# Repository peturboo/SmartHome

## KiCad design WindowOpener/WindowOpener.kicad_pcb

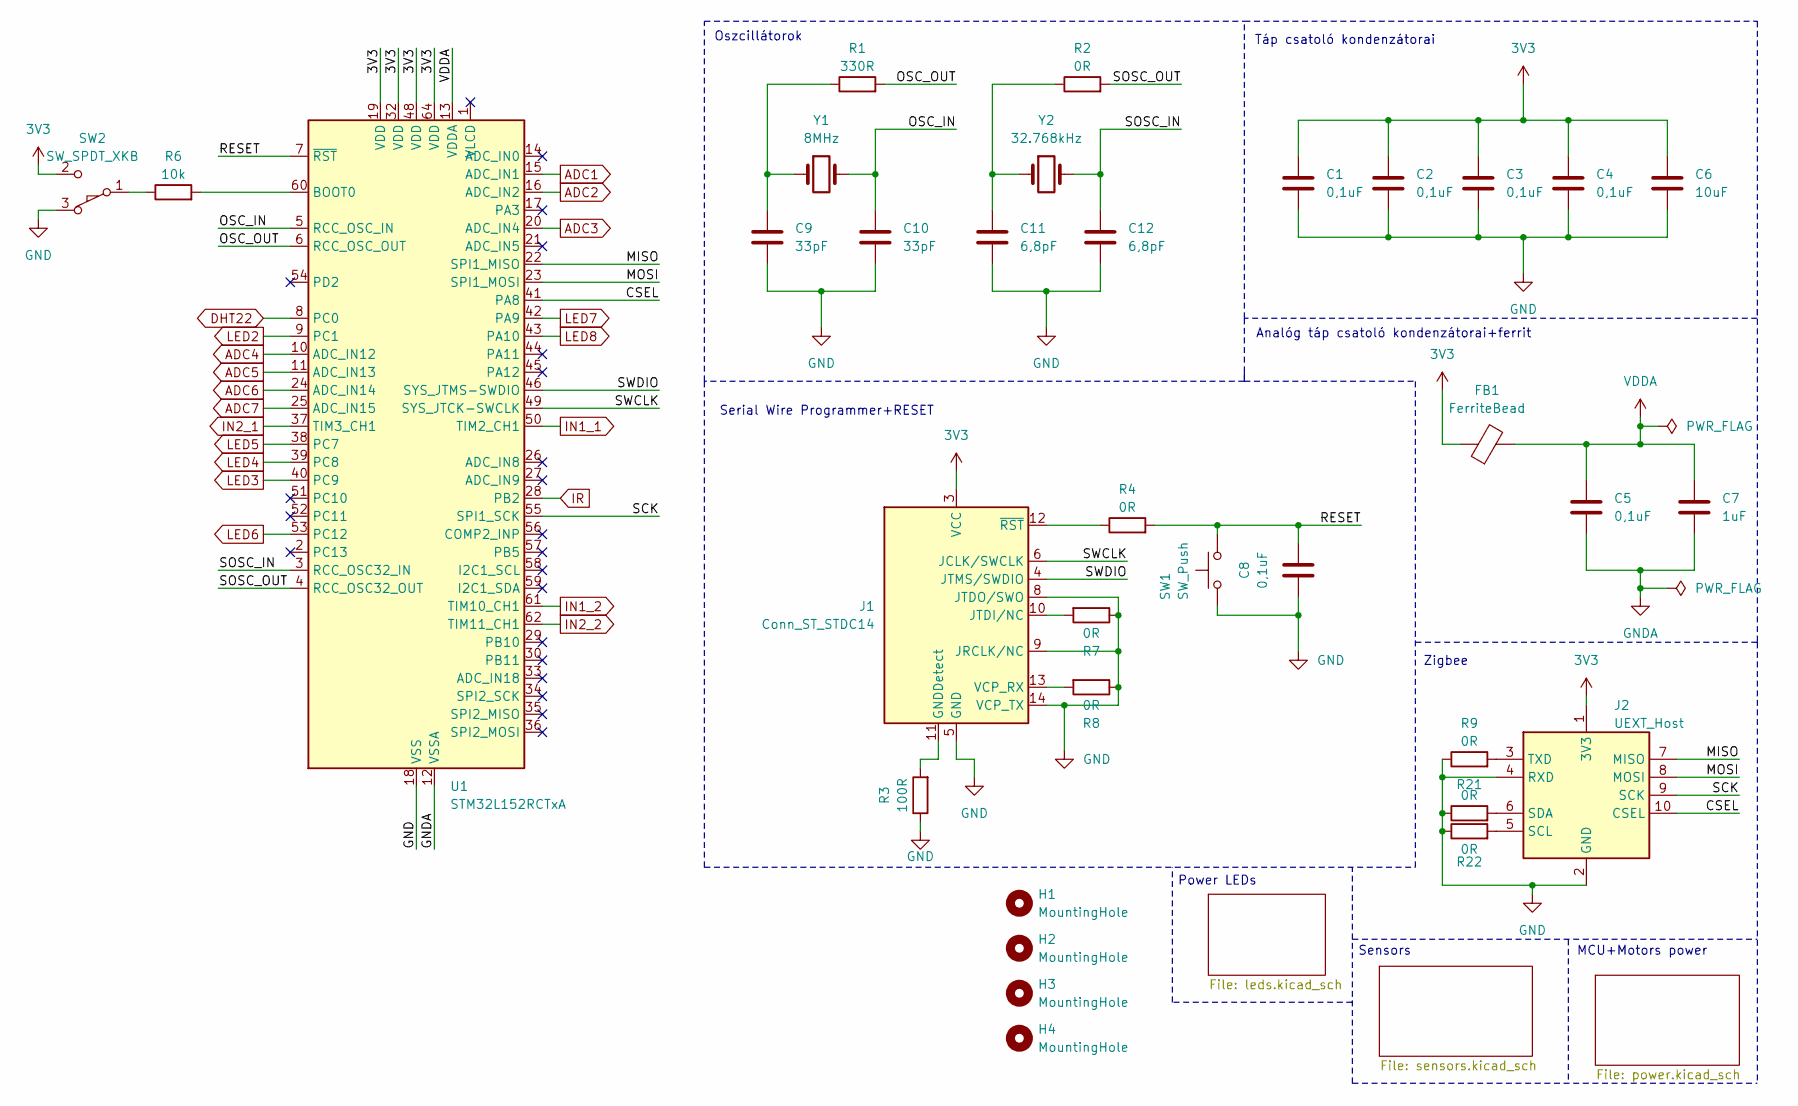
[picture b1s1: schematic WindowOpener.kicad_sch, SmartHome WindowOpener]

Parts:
C1, C2, C3, C4, C5, C8: 0,1uF; C_1206_3216Metric_Pad1.33x1.80mm_HandSolder
C6: 10uF; C_1206_3216Metric_Pad1.33x1.80mm_HandSolder
C7: 1uF; C_2220_5750Metric_Pad1.97x5.40mm_HandSolder
C9, C10: 33pF; C_1206_3216Metric_Pad1.33x1.80mm_HandSolder
C11, C12: 6,8pF; C_1206_3216Metric_Pad1.33x1.80mm_HandSolder
FB1: FerriteBead; L_Axial_L9.5mm_D4.0mm_P12.70mm_Horizontal_Fastron_SMCC
H1, H2, H3, H4: MountingHole; MountingHole_5.3mm_M5
J1: Conn_ST_STDC14; PinHeader_2x07_P1.27mm_Vertical
J2: UEXT_Host; PinHeader_2x05_P2.54mm_Vertical
R1: 330R; R_2010_5025Metric_Pad1.40x2.65mm_HandSolder
R2, R4, R7, R8, R9, R21, R22: 0R; R_2010_5025Metric_Pad1.40x2.65mm_HandSolder
R3: 100R; R_2010_5025Metric_Pad1.40x2.65mm_HandSolder
R6: 10k; R_2010_5025Metric_Pad1.40x2.65mm_HandSolder
SW1: SW_Push; SW_Push_1P1T_NO_CK_KMR2
SW2: SW_SPDT_XKB; SW_XKB_DM1-16UP-1
U1: STM32L152RCTxA; LQFP-64_10x10mm_P0.5mm
Y1: 8MHz; Crystal_HC49-U_Vertical
Y2: 32.768kHz; Crystal_C26-LF_D2.1mm_L6.5mm_Vertical

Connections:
3V3: C1.1, C2.1, C3.1, C4.1, C6.1, FB1.1, J1.3 (VCC), J2.1 (3V3), SW2.2 (B), U1.19 (VDD), U1.32 (VDD), U1.48 (VDD), U1.64 (VDD); also elsewhere on the board
/CSEL: J2.10 (CSEL), U1.41 (PA8)
/MISO: J2.7 (MISO), U1.22 (SPI1_MISO)
/MOSI: J2.8 (MOSI), U1.23 (SPI1_MOSI)
/OSC_IN: C10.1, U1.5 (RCC_OSC_IN), Y1.2
/OSC_OUT: R1.2, U1.6 (RCC_OSC_OUT)
/RESET: C8.2, R4.2, SW1.2, U1.7 (~RST)
/SCK: J2.9 (SCK), U1.55 (SPI1_SCK)
/SOSC_IN: C12.1, U1.3 (RCC_OSC32_IN), Y2.2
/SOSC_OUT: R2.2, U1.4 (RCC_OSC32_OUT)
/SWCLK: J1.6 (JCLK/SWCLK), U1.49 (SYS_JTCK-SWCLK)
/SWDIO: J1.4 (JTMS/SWDIO), U1.46 (SYS_JTMS-SWDIO)
ADC1: U1.15 (ADC_IN1); also elsewhere on the board
ADC2: U1.16 (ADC_IN2); also elsewhere on the board
ADC3: U1.20 (ADC_IN4); also elsewhere on the board
ADC4: U1.10 (ADC_IN12); also elsewhere on the board
ADC5: U1.11 (ADC_IN13); also elsewhere on the board
ADC6: U1.24 (ADC_IN14); also elsewhere on the board
ADC7: U1.25 (ADC_IN15); also elsewhere on the board
DHT22: U1.8 (PC0); also elsewhere on the board
GND: C1.2, C2.2, C3.2, C4.2, C6.2, C8.1, C9.2, C10.2, C11.2, C12.2, J1.5 (GND), J1.7 (GND), J1.8 (JTDO/SWO), J1.9 (JRCLK/NC), J1.14 (VCP_TX), J2.2 (GND), J2.4 (RXD), R3.1, R7.1, R8.1, R9.1, R21.1, R22.1, SW1.1, SW2.3 (C), U1.18 (VSS), U1.31 (VSS), U1.47 (VSS), U1.63 (VSS); also elsewhere on the board
GNDA: C5.2, C7.2, U1.12 (VSSA)
IN1_1: U1.50 (TIM2_CH1); also elsewhere on the board
IN1_2: U1.61 (TIM10_CH1); also elsewhere on the board
IN2_1: U1.37 (TIM3_CH1); also elsewhere on the board
IN2_2: U1.62 (TIM11_CH1); also elsewhere on the board
IR: U1.28 (PB2); also elsewhere on the board
LED2: U1.9 (PC1); also elsewhere on the board
LED3: U1.40 (PC9); also elsewhere on the board
LED4: U1.39 (PC8); also elsewhere on the board
LED5: U1.38 (PC7); also elsewhere on the board
LED6: U1.53 (PC12); also elsewhere on the board
LED7: U1.42 (PA9); also elsewhere on the board
LED8: U1.43 (PA10); also elsewhere on the board
unnamed: C9.1, R1.1, Y1.1
unnamed: C11.1, R2.1, Y2.1
unnamed: J1.11 (GNDDetect), R3.2
unnamed: J1.10 (JTDI/NC), R7.2
unnamed: J1.13 (VCP_RX), R8.2
unnamed: J1.12 (~RST), R4.1
unnamed: J2.5 (SCL), R22.2
unnamed: J2.6 (SDA), R21.2
unnamed: J2.3 (TXD), R9.2
unnamed: R6.1, SW2.1 (A)
unnamed: R6.2, U1.60 (BOOT0)
VDDA: C5.1, C7.1, FB1.2, U1.13 (VDDA)

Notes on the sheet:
Sensors
Zigbee
Serial Wire Programmer+RESET
Analóg táp csatoló kondenzátorai+ferrit
Oszcillátorok
MCU+Motors power
Táp csatoló kondenzátorai
Power LEDs

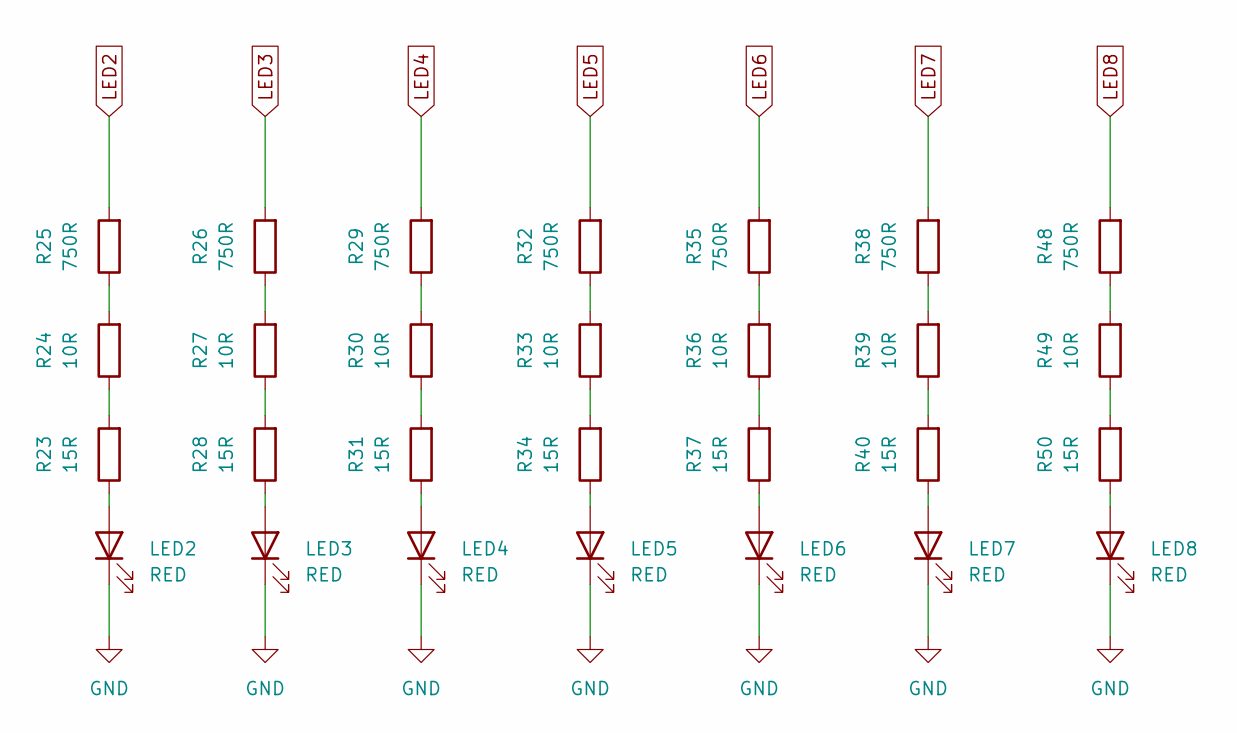
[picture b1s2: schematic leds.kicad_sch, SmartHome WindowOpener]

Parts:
LED2, LED3, LED4, LED5, LED6, LED7, LED8: RED; LED_1206_3216Metric_Pad1.42x1.75mm_HandSolder
R23, R28, R31, R34, R37, R40, R50: 15R; R_1210_3225Metric_Pad1.30x2.65mm_HandSolder
R24, R27, R30, R33, R36, R39, R49: 10R; R_1206_3216Metric_Pad1.30x1.75mm_HandSolder
R25, R26, R29, R32, R35, R38, R48: 750R; R_1206_3216Metric_Pad1.30x1.75mm_HandSolder

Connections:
GND: LED2.1 (K), LED3.1 (K), LED4.1 (K), LED5.1 (K), LED6.1 (K), LED7.1 (K), LED8.1 (K); also elsewhere on the board
LED2: R25.2; also elsewhere on the board
LED3: R26.2; also elsewhere on the board
LED4: R29.2; also elsewhere on the board
LED5: R32.2; also elsewhere on the board
LED6: R35.2; also elsewhere on the board
LED7: R38.2; also elsewhere on the board
LED8: R48.2; also elsewhere on the board
unnamed: LED2.2 (A), R23.1
unnamed: LED3.2 (A), R28.1
unnamed: LED4.2 (A), R31.1
unnamed: LED5.2 (A), R34.1
unnamed: LED6.2 (A), R37.1
unnamed: LED7.2 (A), R40.1
unnamed: LED8.2 (A), R50.1
unnamed: R23.2, R24.1
unnamed: R24.2, R25.1
unnamed: R26.1, R27.2
unnamed: R27.1, R28.2
unnamed: R29.1, R30.2
unnamed: R30.1, R31.2
unnamed: R32.1, R33.2
unnamed: R33.1, R34.2
unnamed: R35.1, R36.2
unnamed: R36.1, R37.2
unnamed: R38.1, R39.2
unnamed: R39.1, R40.2
unnamed: R48.1, R49.2
unnamed: R49.1, R50.2

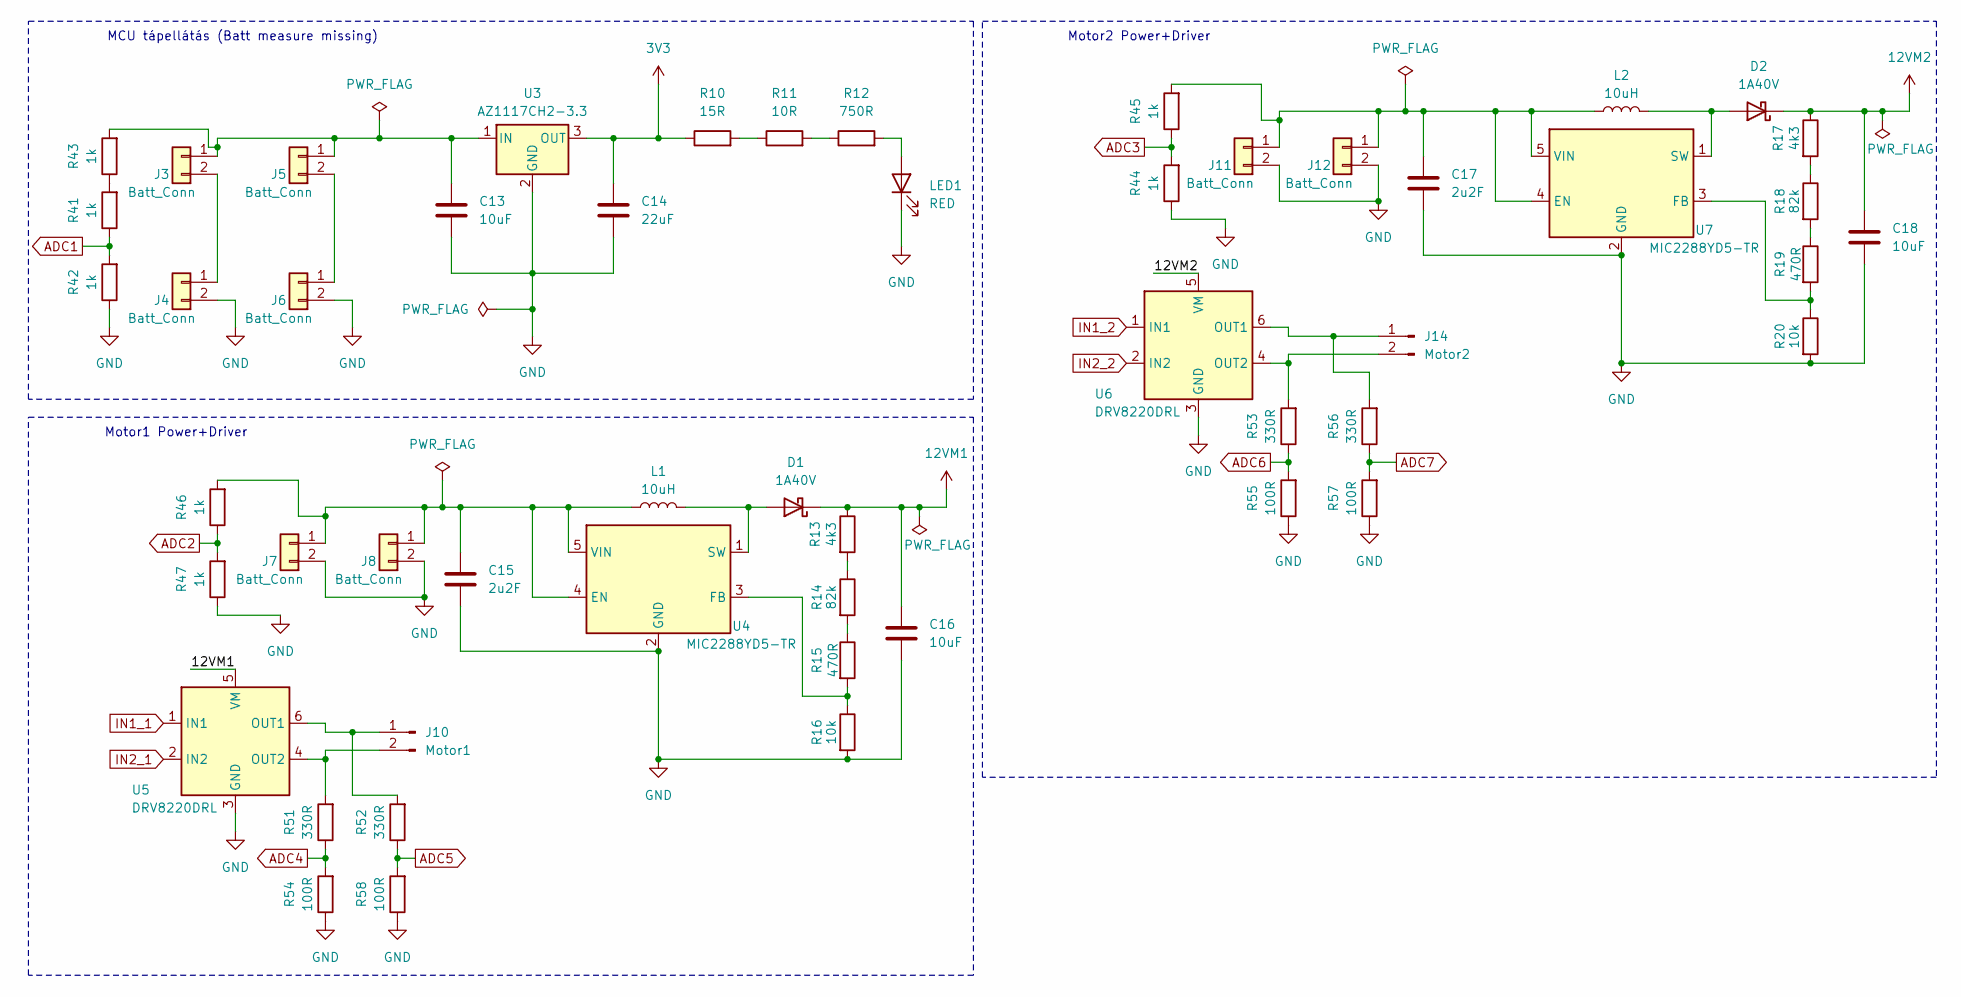
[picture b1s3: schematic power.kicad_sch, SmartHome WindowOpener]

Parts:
C13, C16, C18: 10uF; C_1206_3216Metric_Pad1.33x1.80mm_HandSolder
C14: 22uF; C_1206_3216Metric_Pad1.33x1.80mm_HandSolder
C15, C17: 2u2F; C_1206_3216Metric_Pad1.33x1.80mm_HandSolder
D1, D2: 1A40V; 1N5819HW-7-F
J3, J4, J5, J6, J7, J8, J11, J12: Batt_Conn; BatteryHolder_Keystone_1042_1x18650
J10: Motor1; PinHeader_1x02_P2.54mm_Vertical
J14: Motor2; PinHeader_1x02_P2.54mm_Vertical
L1, L2: 10uH; L_1210_3225Metric_Pad1.42x2.65mm_HandSolder
LED1: RED; LED_1206_3216Metric_Pad1.42x1.75mm_HandSolder
R10: 15R; R_1210_3225Metric_Pad1.30x2.65mm_HandSolder
R11: 10R; R_1206_3216Metric_Pad1.30x1.75mm_HandSolder
R12: 750R; R_1206_3216Metric_Pad1.30x1.75mm_HandSolder
R13, R17: 4k3; R_1206_3216Metric_Pad1.30x1.75mm_HandSolder
R14, R18: 82k; R_1206_3216Metric_Pad1.30x1.75mm_HandSolder
R15, R19: 470R; R_1206_3216Metric_Pad1.30x1.75mm_HandSolder
R16, R20: 10k; R_2010_5025Metric_Pad1.40x2.65mm_HandSolder
R41, R42, R43, R44, R45, R46, R47: 1k; R_2010_5025Metric_Pad1.40x2.65mm_HandSolder
R51, R52, R53, R56: 330R; R_2010_5025Metric_Pad1.40x2.65mm_HandSolder
R54, R55, R57, R58: 100R; R_2010_5025Metric_Pad1.40x2.65mm_HandSolder
U3: AZ1117CH2-3.3; SOT-223-3_TabPin2
U4, U7: MIC2288YD5-TR; TSOT-23-5_HandSoldering
U5, U6: DRV8220DRL; SOT-563

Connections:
3V3: C14.1, R10.1, U3.3 (OUT); also elsewhere on the board
12VM1: C16.1, D1.1 (K), R13.1, U5.5 (VM)
12VM2: C18.1, D2.1 (K), R17.1, U6.5 (VM)
ADC1: R41.1, R42.2; also elsewhere on the board
ADC2: R46.1, R47.2; also elsewhere on the board
ADC3: R44.2, R45.1; also elsewhere on the board
ADC4: R51.1, R54.2; also elsewhere on the board
ADC5: R52.1, R58.2; also elsewhere on the board
ADC6: R53.1, R55.2; also elsewhere on the board
ADC7: R56.1, R57.2; also elsewhere on the board
GND: C13.2, C14.2, C15.2, C16.2, C17.2, C18.2, J4.2 (Positve), J6.2 (Positve), J7.2 (Positve), J8.2 (Positve), J11.2 (Positve), J12.2 (Positve), LED1.1 (K), R16.2, R20.2, R42.1, R44.1, R47.1, R54.1, R55.1, R57.1, R58.1, U3.2 (GND), U4.2 (GND), U5.3 (GND), U6.3 (GND), U7.2 (GND); also elsewhere on the board
IN1_1: U5.1 (IN1); also elsewhere on the board
IN1_2: U6.1 (IN1); also elsewhere on the board
IN2_1: U5.2 (IN2); also elsewhere on the board
IN2_2: U6.2 (IN2); also elsewhere on the board
unnamed: D1.2 (A), L1.2, U4.1 (SW)
unnamed: D2.2 (A), L2.2, U7.1 (SW)
unnamed: J3.2 (Positve), J4.1 (Negative)
unnamed: C13.1, J3.1 (Negative), J5.1 (Negative), R43.2, U3.1 (IN)
unnamed: J5.2 (Positve), J6.1 (Negative)
unnamed: C15.1, J7.1 (Negative), J8.1 (Negative), L1.1, R46.2, U4.4 (EN), U4.5 (VIN)
unnamed: J10.2 (Pin_1), R51.2, U5.4 (OUT2)
unnamed: J10.1 (Pin_2), R52.2, U5.6 (OUT1)
unnamed: C17.1, J11.1 (Negative), J12.1 (Negative), L2.1, R45.2, U7.4 (EN), U7.5 (VIN)
unnamed: J14.2 (Pin_1), R53.2, U6.4 (OUT2)
unnamed: J14.1 (Pin_2), R56.2, U6.6 (OUT1)
unnamed: LED1.2 (A), R12.2
unnamed: R10.2, R11.1
unnamed: R11.2, R12.1
unnamed: R13.2, R14.1
unnamed: R14.2, R15.1
unnamed: R17.2, R18.1
unnamed: R18.2, R19.1
unnamed: R41.2, R43.1
unnamed: R15.2, R16.1, U4.3 (FB)
unnamed: R19.2, R20.1, U7.3 (FB)

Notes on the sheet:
Motor1 Power+Driver
Motor2 Power+Driver
MCU tápellátás (Batt measure missing)

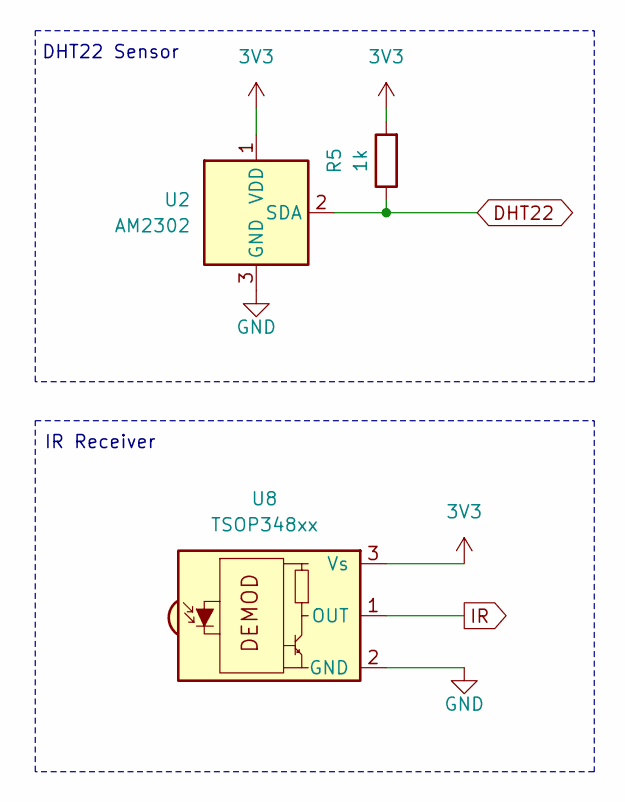
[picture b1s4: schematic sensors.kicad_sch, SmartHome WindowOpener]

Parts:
R5: 1k; R_2010_5025Metric_Pad1.40x2.65mm_HandSolder
U2: AM2302; ASAIR_AM2302_P2.54mm_Vertical
U8: TSOP348xx; Vishay_MOLD-3Pin

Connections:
3V3: R5.2, U2.1 (VDD), U8.3 (Vs); also elsewhere on the board
DHT22: R5.1, U2.2 (SDA); also elsewhere on the board
GND: U2.3 (GND), U2.4 (GND), U8.2 (GND); also elsewhere on the board
IR: U8.1 (OUT); also elsewhere on the board

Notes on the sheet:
DHT22 Sensor
IR Receiver

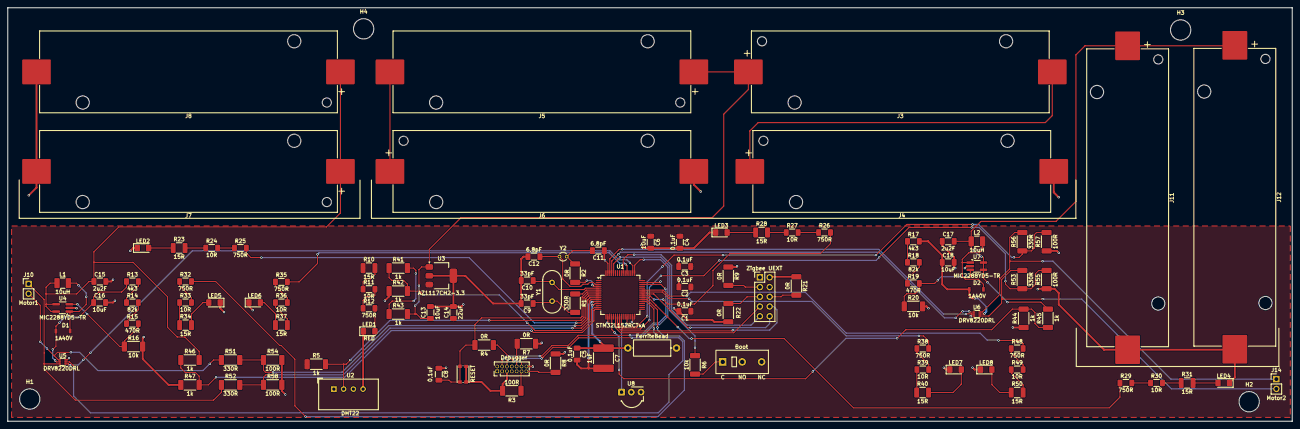
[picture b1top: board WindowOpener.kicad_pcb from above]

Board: 2 copper layers, 335.5 x 108.0 mm, 117 parts (0 on the bottom side), 90 nets.

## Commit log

2026-03-08 SmartHome repo
2026-03-08 Power hozzáadva
2026-03-10 v0.1
2026-03-21 v0.2
2026-03-21 v0.3
2026-03-30 v0.4
2026-03-31 v0.5
2026-03-31 v0.6
2026-04-04 v0.7
2026-04-04 v1.0
2026-04-05 v1.0.1
2026-04-08 v1.0.2
2026-04-08 v1.0.3
2026-04-08 v1.0.4
